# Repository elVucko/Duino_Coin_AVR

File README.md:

# Read Me 

---

## Description

This is the simplest DUINO coin mining board design with four Atmega328p and CH340 connected to the FE1.1S USB hub. All that's needed to mine with this board is a micro USB/USB A cable to connect with a computer and the AVR_Miner application installed. 
One version of the PCB is with CH340C and for me, that version works great. But only the CH340C can be used here. Due to difficulties in buying quality chips, I did another design where CH340G is used. On this PCB, both versions of CH340 can be used without any problems. I made this design for fun and I hope it can be useful to someone.

All information regarding the DUINO can be found on the official website:

- https://duinocoin.com/
- https://duinocoin.com/getting-started
- https://github.com/revoxhere/duino-coin/releases/

---

### If you want to support my work

- https://paypal.me/elvuckoo
- https://explorer.duinocoin.com/?search=Vucko

---

## Author Info

- Freelancer - https://www.freelancer.com/hireme/dvucko

[Back To The Top](#read-me-template)

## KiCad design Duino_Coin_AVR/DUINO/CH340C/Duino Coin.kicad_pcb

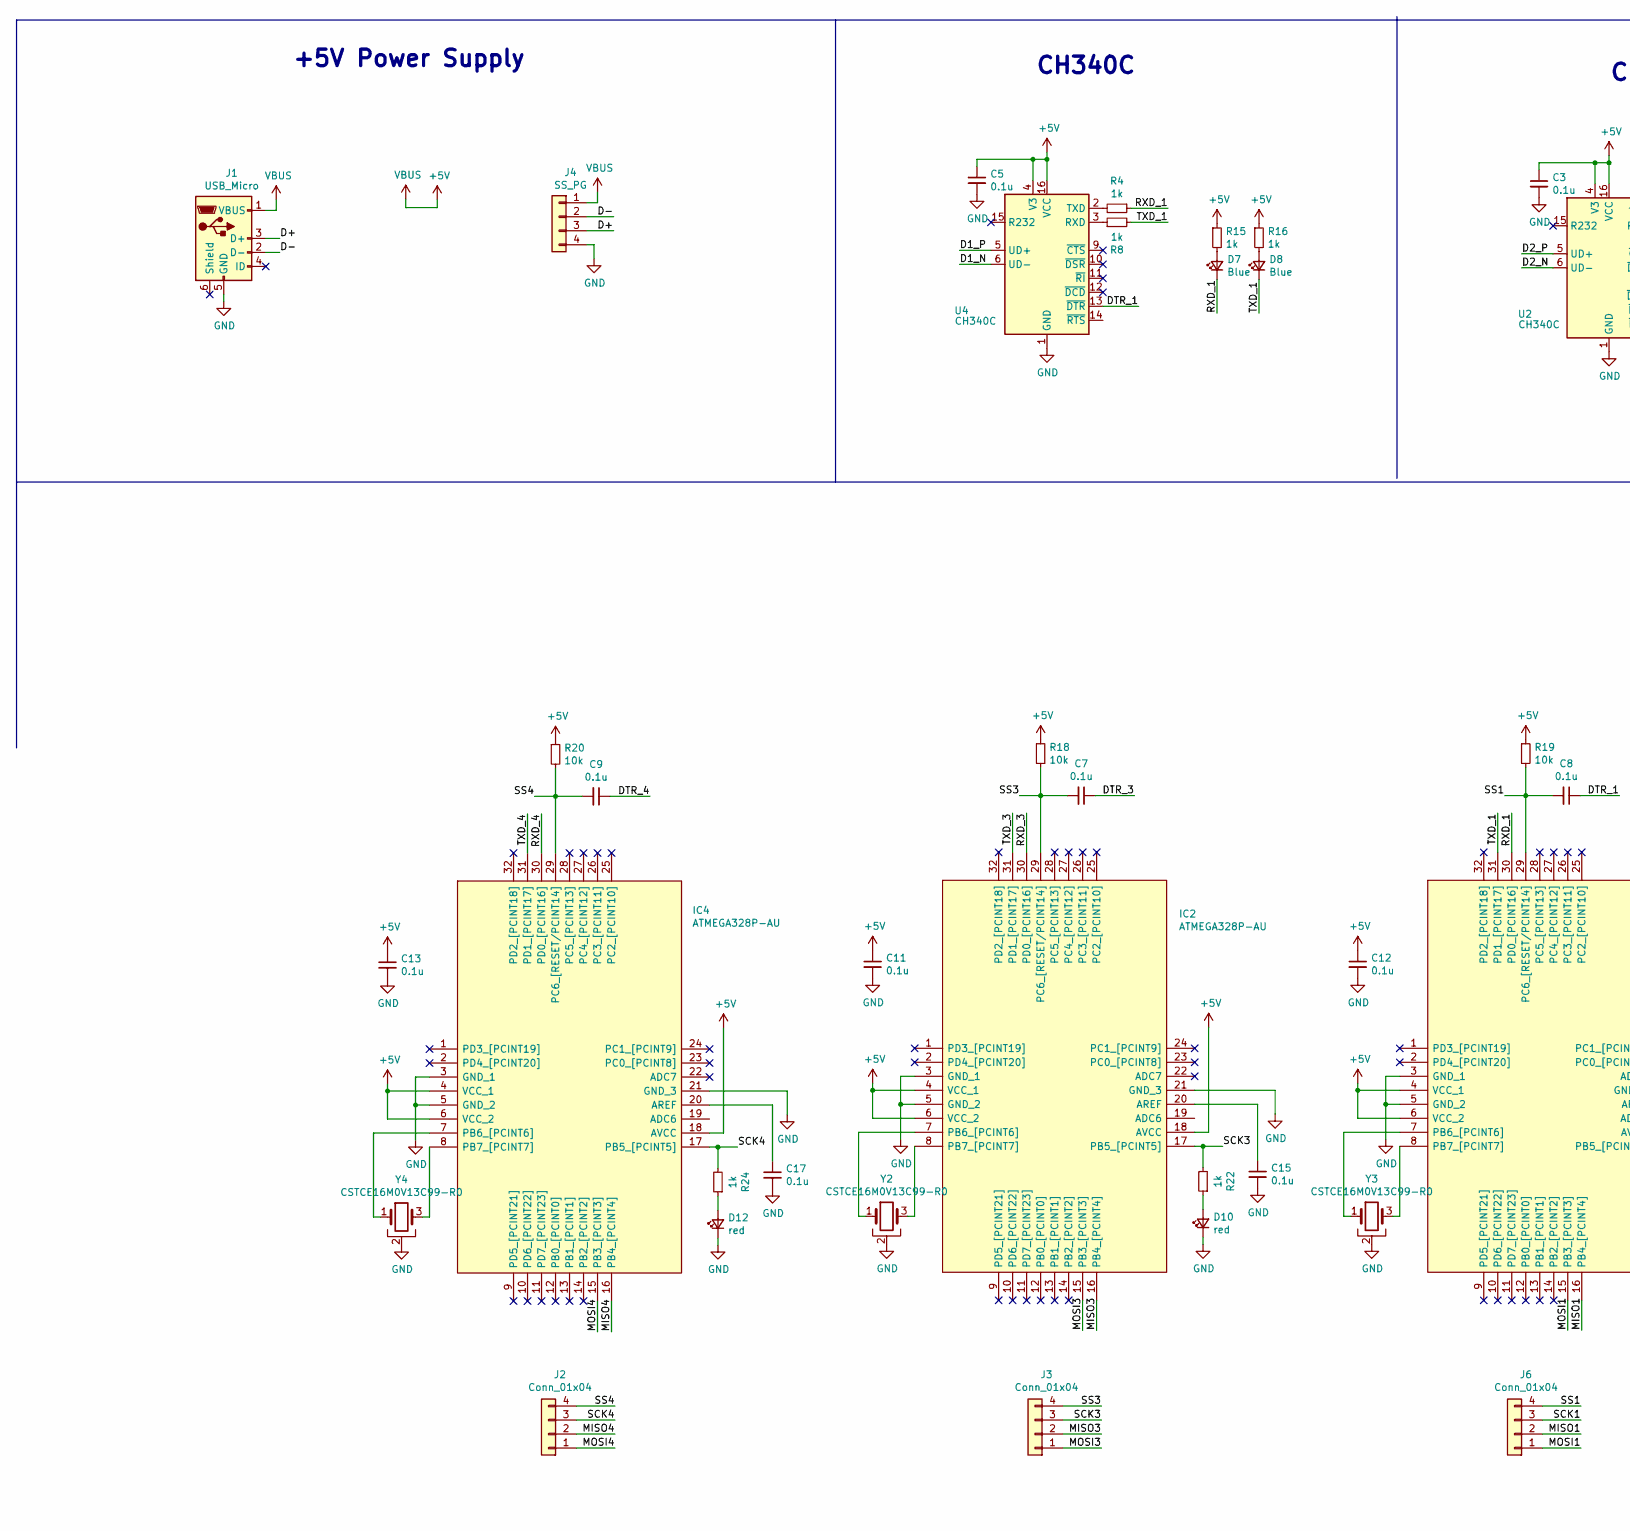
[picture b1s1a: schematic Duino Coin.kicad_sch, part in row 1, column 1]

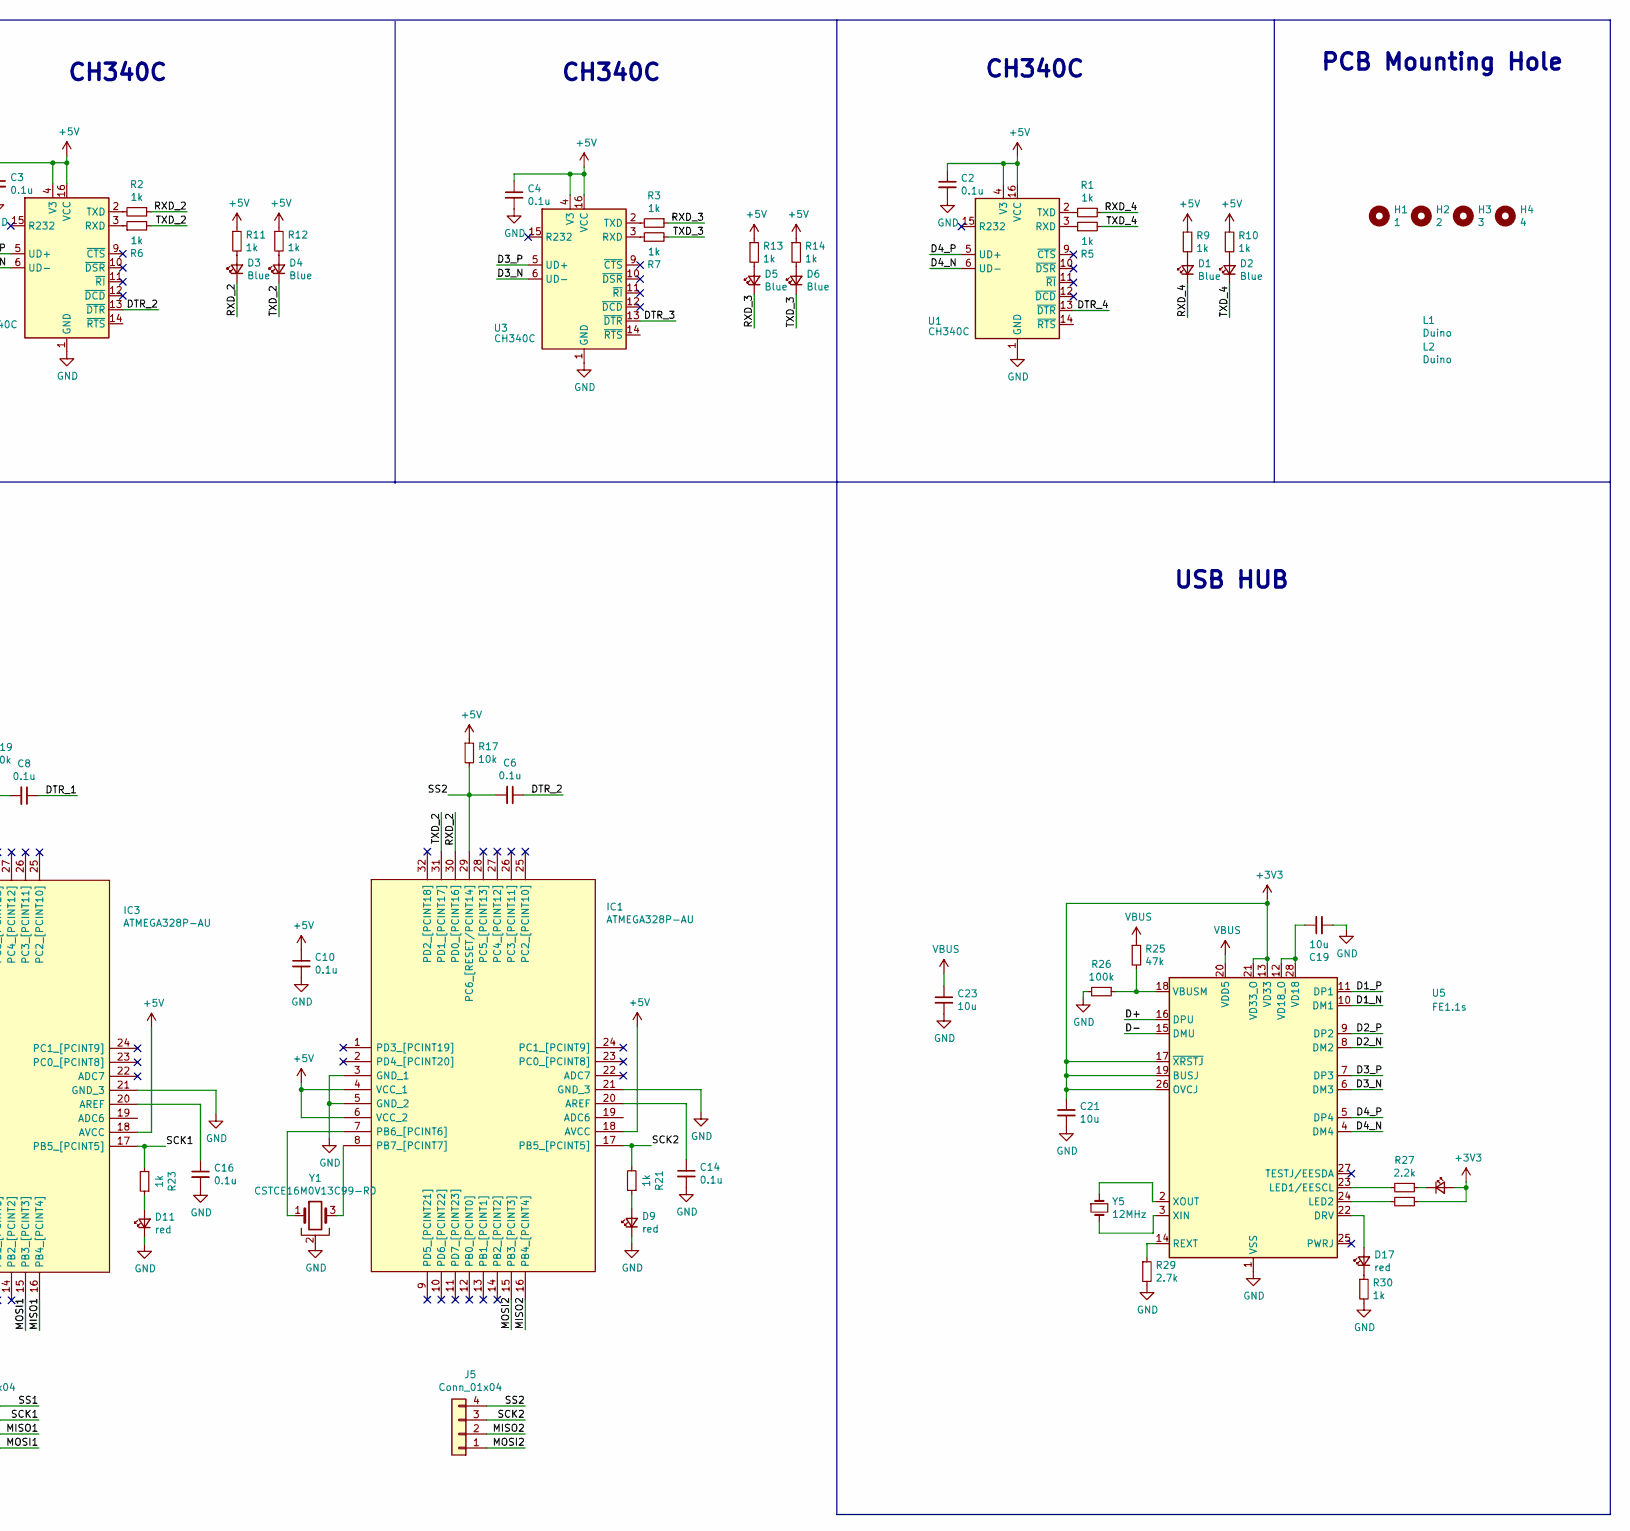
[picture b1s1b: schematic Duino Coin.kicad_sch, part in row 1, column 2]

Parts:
C2, C3, C4, C5, C6, C7, C8, C9, C10, C11, C12, C13, C14, C15, C16, C17: 0.1u; C_0805_2012Metric_Pad1.18x1.45mm_HandSolder
C19, C21, C23: 10u; C_0805_2012Metric_Pad1.18x1.45mm_HandSolder
D1, D2, D3, D4, D5, D6, D7, D8: Blue; LED_0603_1608Metric_Pad1.05x0.95mm_HandSolder
D9, D10, D11, D12, D17: red; LED_0603_1608Metric_Pad1.05x0.95mm_HandSolder
D13: 2; LED_0603_1608Metric_Pad1.05x0.95mm_HandSolder
H1: 1; MountingHole_3.2mm_M3
H2: 2; MountingHole_3.2mm_M3
H3: 3; MountingHole_3.2mm_M3
H4: 4; MountingHole_3.2mm_M3
IC1, IC2, IC3, IC4: ATMEGA328P-AU; QFP80P900X900X120-32N; Manufacturer_Part_Number ATMEGA328P-AU; Mouser Part Number 556-ATMEGA328P-AU
J1: USB_Micro; USB_Micro-B_Amphenol_10104110_Horizontal
J2, J3, J5, J6: Conn_01x04; PinHeader_1x04_P2.54mm_Vertical
J4: SS_PG; PinHeader_1x04_P2.54mm_Horizontal
L1, L2: Duino
R1, R2, R3, R4, R5, R6, R7, R8: 1k; R_0603_1608Metric_Pad0.98x0.95mm_HandSolder
R9, R10, R11, R12, R13, R14, R15, R16, R21, R22, R23, R24, R30: 1k; R_0805_2012Metric_Pad1.20x1.40mm_HandSolder
R17, R18, R19, R20: 10k; R_0805_2012Metric_Pad1.20x1.40mm_HandSolder
R25: 47k; R_0805_2012Metric_Pad1.20x1.40mm_HandSolder
R26: 100k; R_0805_2012Metric_Pad1.20x1.40mm_HandSolder
R27, R28: 2.2k; R_0805_2012Metric_Pad1.20x1.40mm_HandSolder
R29: 2.7k; R_0805_2012Metric_Pad1.20x1.40mm_HandSolder
U1, U2, U3, U4: CH340C; SOIC-16_3.9x9.9mm_P1.27mm
U5: FE1.1s; SSOP-28_3.9x9.9mm_P0.635mm
Y1, Y2, Y3, Y4: CSTCE16M0V13C99-R0; OSC_CSTCE8M00G55-R0
Y5: 12MHz; Crystal_SMD_5032-2Pin_5.0x3.2mm

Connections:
+3V3: C21.1, D13.2 (A), R28.1, U5.13 (VD33), U5.17 (~XRSTJ), U5.19 (BUSJ), U5.21 (VD33_O), U5.26 (OVCJ)
+5V: C2.1, C3.1, C4.1, C5.1, C10.1, C11.1, C12.1, C13.1, C23.1, IC1.4 (VCC_1), IC1.6 (VCC_2), IC1.18 (AVCC), IC2.4 (VCC_1), IC2.6 (VCC_2), IC2.18 (AVCC), IC3.4 (VCC_1), IC3.6 (VCC_2), IC3.18 (AVCC), IC4.4 (VCC_1), IC4.6 (VCC_2), IC4.18 (AVCC), J1.1 (VBUS), J4.1, R9.1, R10.1, R11.1, R12.1, R13.1, R14.1, R15.1, R16.1, R17.1, R18.1, R19.1, R20.1, R25.1, U1.4 (V3), U1.16 (VCC), U2.4 (V3), U2.16 (VCC), U3.4 (V3), U3.16 (VCC), U4.4 (V3), U4.16 (VCC), U5.20 (VDD5)
/D1_N: U4.6 (UD-), U5.10 (DM1)
/D1_P: U4.5 (UD+), U5.11 (DP1)
/D2_N: U2.6 (UD-), U5.8 (DM2)
/D2_P: U2.5 (UD+), U5.9 (DP2)
/D3_N: U3.6 (UD-), U5.6 (DM3)
/D3_P: U3.5 (UD+), U5.7 (DP3)
/D4_N: U1.6 (UD-), U5.4 (DM4)
/D4_P: U1.5 (UD+), U5.5 (DP4)
/D+: J1.3 (D+), J4.3, U5.16 (DPU)
/D-: J1.2 (D-), J4.2, U5.15 (DMU)
/DTR_1: C8.1, U4.13 (~DTR)
/DTR_2: C6.1, U2.13 (~DTR)
/DTR_3: C7.1, U3.13 (~DTR)
/DTR_4: C9.1, U1.13 (~DTR)
/MISO1: IC3.16 (PB4_[PCINT4]), J6.2
/MISO2: IC1.16 (PB4_[PCINT4]), J5.2
/MISO3: IC2.16 (PB4_[PCINT4]), J3.2
/MISO4: IC4.16 (PB4_[PCINT4]), J2.2
/MOSI1: IC3.15 (PB3_[PCINT3]), J6.1
/MOSI2: IC1.15 (PB3_[PCINT3]), J5.1
/MOSI3: IC2.15 (PB3_[PCINT3]), J3.1
/MOSI4: IC4.15 (PB3_[PCINT3]), J2.1
/RXD_1: D7.1 (K), IC3.30 (PD0_[PCINT16]), R4.1
/RXD_2: D3.1 (K), IC1.30 (PD0_[PCINT16]), R2.1
/RXD_3: D5.1 (K), IC2.30 (PD0_[PCINT16]), R3.1
/RXD_4: D1.1 (K), IC4.30 (PD0_[PCINT16]), R1.1
/SCK1: IC3.17 (PB5_[PCINT5]), J6.3, R23.2
/SCK2: IC1.17 (PB5_[PCINT5]), J5.3, R21.2
/SCK3: IC2.17 (PB5_[PCINT5]), J3.3, R22.2
/SCK4: IC4.17 (PB5_[PCINT5]), J2.3, R24.2
/SS1: C8.2, IC3.29 (PC6_[RESET/PCINT14]), J6.4, R19.2
/SS2: C6.2, IC1.29 (PC6_[RESET/PCINT14]), J5.4, R17.2
/SS3: C7.2, IC2.29 (PC6_[RESET/PCINT14]), J3.4, R18.2
/SS4: C9.2, IC4.29 (PC6_[RESET/PCINT14]), J2.4, R20.2
/TXD_1: D8.1 (K), IC3.31 (PD1_[PCINT17]), R8.2
/TXD_2: D4.1 (K), IC1.31 (PD1_[PCINT17]), R6.2
/TXD_3: D6.1 (K), IC2.31 (PD1_[PCINT17]), R7.2
/TXD_4: D2.1 (K), IC4.31 (PD1_[PCINT17]), R5.2
GND: C2.2, C3.2, C4.2, C5.2, C10.2, C11.2, C12.2, C13.2, C14.2, C15.2, C16.2, C17.2, C19.2, C21.2, C23.2, D9.1 (K), D10.1 (K), D11.1 (K), D12.1 (K), IC1.3 (GND_1), IC1.5 (GND_2), IC1.21 (GND_3), IC2.3 (GND_1), IC2.5 (GND_2), IC2.21 (GND_3), IC3.3 (GND_1), IC3.5 (GND_2), IC3.21 (GND_3), IC4.3 (GND_1), IC4.5 (GND_2), IC4.21 (GND_3), J1.5 (GND), J4.4, R26.2, R29.2, R30.2, U1.1 (GND), U2.1 (GND), U3.1 (GND), U4.1 (GND), U5.1 (VSS), Y1.2, Y2.2, Y3.2, Y4.2
unnamed: C14.1, IC1.20 (AREF)
unnamed: C15.1, IC2.20 (AREF)
unnamed: C16.1, IC3.20 (AREF)
unnamed: C17.1, IC4.20 (AREF)
unnamed: C19.1, U5.12 (VD18_O), U5.28 (VD18)
unnamed: D1.2 (A), R9.2
unnamed: D2.2 (A), R10.2
unnamed: D3.2 (A), R11.2
unnamed: D4.2 (A), R12.2
unnamed: D5.2 (A), R13.2
unnamed: D6.2 (A), R14.2
unnamed: D7.2 (A), R15.2
unnamed: D8.2 (A), R16.2
unnamed: D9.2 (A), R21.1
unnamed: D10.2 (A), R22.1
unnamed: D11.2 (A), R23.1
unnamed: D12.2 (A), R24.1
unnamed: D13.1 (K), R27.1
unnamed: D17.1 (K), R30.1
unnamed: D17.2 (A), U5.22 (DRV)
unnamed: IC1.7 (PB6_[PCINT6]), Y1.1
unnamed: IC1.8 (PB7_[PCINT7]), Y1.3
unnamed: IC2.7 (PB6_[PCINT6]), Y2.1
unnamed: IC2.8 (PB7_[PCINT7]), Y2.3
unnamed: IC3.7 (PB6_[PCINT6]), Y3.1
unnamed: IC3.8 (PB7_[PCINT7]), Y3.3
unnamed: IC4.7 (PB6_[PCINT6]), Y4.1
unnamed: IC4.8 (PB7_[PCINT7]), Y4.3
unnamed: R1.2, U1.2 (TXD)
unnamed: R2.2, U2.2 (TXD)
unnamed: R3.2, U3.2 (TXD)
unnamed: R4.2, U4.2 (TXD)
unnamed: R5.1, U1.3 (RXD)
unnamed: R6.1, U2.3 (RXD)
unnamed: R7.1, U3.3 (RXD)
unnamed: R8.1, U4.3 (RXD)
unnamed: R25.2, R26.1, U5.18 (VBUSM)
unnamed: R27.2, U5.23 (LED1/EESCL)
unnamed: R28.2, U5.24 (LED2)
unnamed: R29.1, U5.14 (REXT)
unnamed: U5.2 (XOUT), Y5.1
unnamed: U5.3 (XIN), Y5.2

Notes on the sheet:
CH340C
+5V Power Supply
PCB Mounting Hole
USB HUB

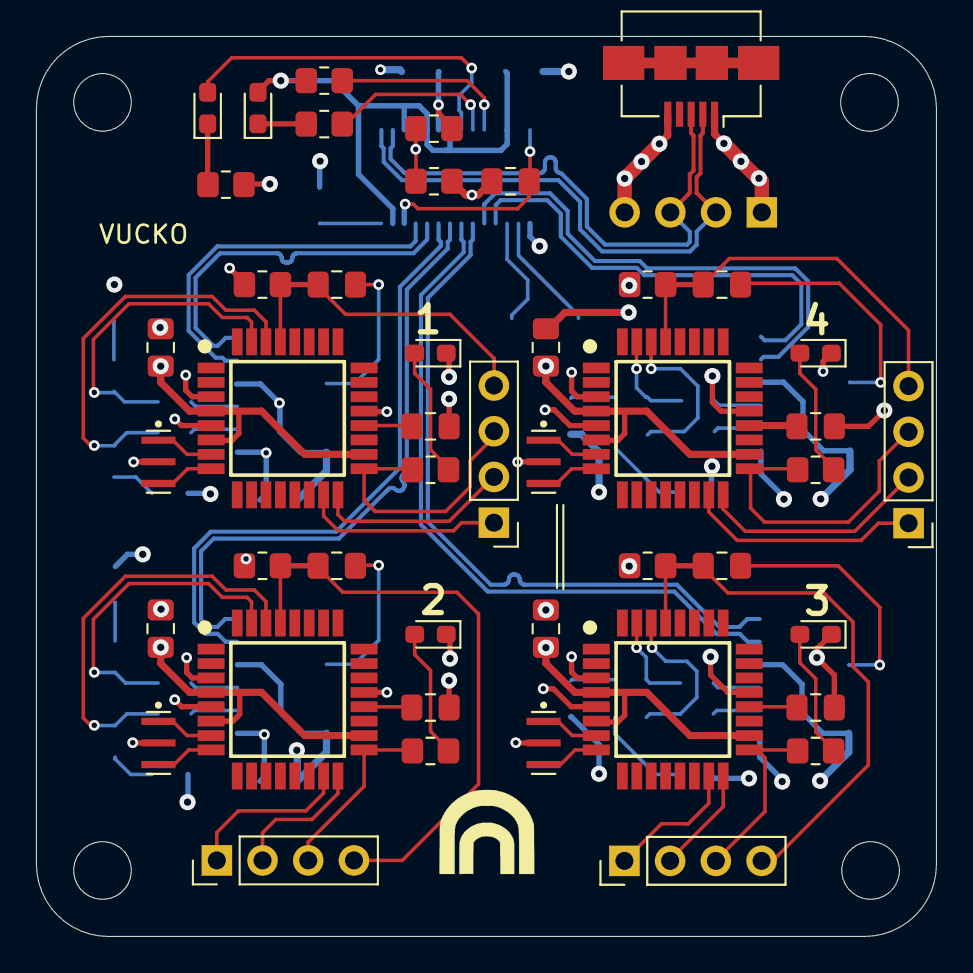
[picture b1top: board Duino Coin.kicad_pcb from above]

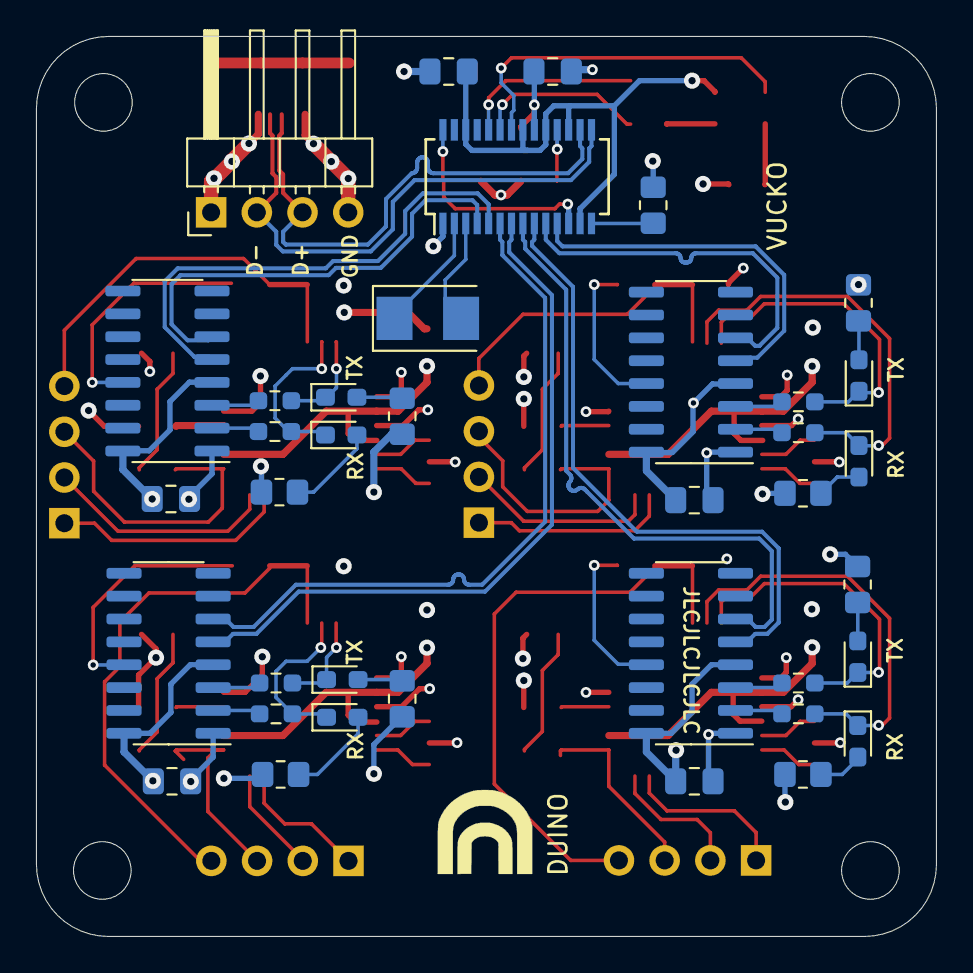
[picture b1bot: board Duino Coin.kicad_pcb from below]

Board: 4 copper layers, 50.0 x 50.0 mm, 89 parts (39 on the bottom side), 83 nets.

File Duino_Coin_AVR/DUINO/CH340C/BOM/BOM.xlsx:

Id | Designator | Package | Quantity | Designation | Mouser
1 | C6,C7,C8,C9,C10,C11,C12,C13,C14,C15,C16,C17,C2,C3,C4,C5 | C_0805_2012Metric_Pad1.18x1.45mm | 16 | 0.1u
2 | C19,C21,C23 | C_0805_2012Metric_Pad1.18x1.45mm | 3 | 10u
3 | R17,R18,R19,R20 | R_0805_2012Metric_Pad1.20x1.40mm | 4 | 10k
4 | R21,R22,R23,R24,R30,R9,R10,R11,R12,R13,R14,R15,R16 | R_0805_2012Metric_Pad1.20x1.40mm | 13 | 1k
5 | R25 | R_0805_2012Metric_Pad1.20x1.40mm | 1 | 47k
6 | R26 | R_0805_2012Metric_Pad1.20x1.40mm | 1 | 100k
7 | R29 | R_0805_2012Metric_Pad1.20x1.40mm | 1 | 2.7k
8 | R1,R2,R3,R4,R5,R6,R7,R8 | R_0603_1608Metric_Pad0.98x0.95mm | 8 | 1k
9 | R27,R28 | R_0805_2012Metric_Pad1.20x1.40mm | 2 | 2.2k
10 | D1,D2,D3,D4,D5,D6,D7,D8 | LED_0603_1608Metric_Pad1.05x0.95mm | 8 | Blue
11 | D9,D10,D11,D12 | LED_0603_1608Metric_Pad1.05x0.95mm | 4 | red
12 | D13,D17 | LED_0603_1608Metric_Pad1.05x0.95mm | 2 | Green
13 | U1,U2,U3,U4 | SOIC-16_3.9x9.9mm_P1.27mm | 4 | CH340C
14 | U5 | SSOP-28_3.9x9.9mm_P0.635mm | 1 | FE1.1s
15 | IC1,IC2,IC4,IC3 | QFP80P900X900X120-32N | 4 | ATMEGA328P-AU
16 | Y1,Y2,Y3,Y4 | OSC_CSTCE8M00G55-R0 | 4 | CSTCE16M0V13C99-R0 | 81-CSTCE16M0V13C99R0
17 | Y5 | Crystal_SMD_5032-2Pin_5.0x3.2mm | 1 | 12MHz | 344-NX5032GA12MLNCD1
18 | J1 | USB_Micro-B_Amphenol_10104110 | 1 | USB_Micro | 649-10104110-0001LF
19 | J2,J3,J5,J6 | PinHeader_1x04_P2.54mm_Vertical | 4 | Conn_01x04
20 | J4 | PinHeader_1x04_P2.54mm_Horizontal | 1 | SS_PG
